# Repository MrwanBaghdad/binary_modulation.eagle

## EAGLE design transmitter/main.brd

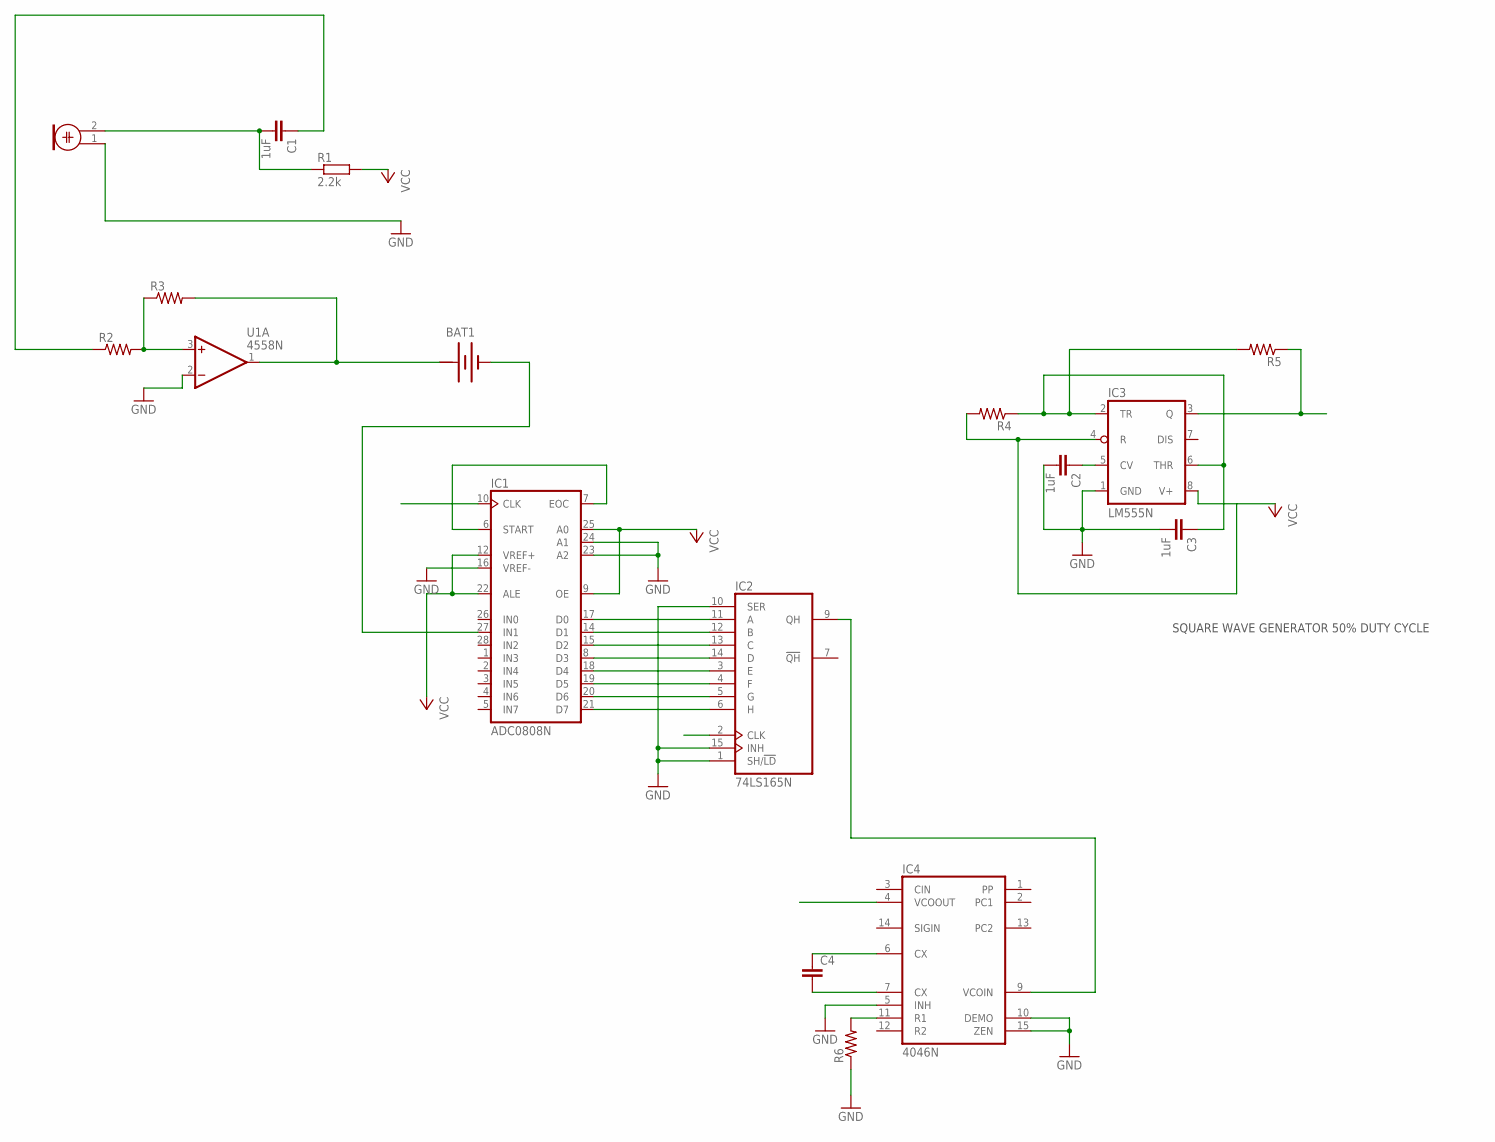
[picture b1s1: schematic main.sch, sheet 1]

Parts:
BAT1: BATTERY
C1, C2, C3: 1uF; C2.5-3
C4: C2.5/2; C2.5-2
IC1: ADC0808N; DIL28-6
IC2: 74LS165N; DIL16
IC3: LM555N; DIL08-ROUND
IC4: 4046N; DIL16
M1: ELECTRET_MICROPHON-F6050AP; F6050AP
R1: 2.2k; 0204/7
R2, R3, R4, R5, R6: R-US_0204/7; 0204/7
U1: 4558N; DIL08

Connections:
+: BAT1.+@1 (+)
CLK: IC1.10 (CLK), IC2.2 (CLK), IC3.3 (Q), R5.1
GND: C2.2, C3.2, IC1.13 (GND), IC1.16 (VREF-), IC1.23 (A2), IC1.24 (A1), IC2.1 (SH/!LD), IC2.8 (GND), IC2.10 (SER), IC2.15 (INH), IC3.1 (GND), IC4.5 (INH), IC4.10 (DEMO), IC4.15 (ZEN), M1.1, R6.1, U1.2 (-IN)
unnamed: C1.2, M1.2, R1.1
unnamed: C1.1, R2.1
unnamed: R2.2, R3.1, U1.3 (+IN)
unnamed: BAT1.+, R3.2, U1.1 (OUT)
unnamed: BAT1.-, IC1.27 (IN1)
unnamed: IC1.6 (START), IC1.7 (EOC)
unnamed: IC1.17 (D0), IC2.11 (A)
unnamed: IC1.14 (D1), IC2.12 (B)
unnamed: IC1.15 (D2), IC2.13 (C)
unnamed: IC1.8 (D3), IC2.14 (D)
unnamed: IC1.18 (D4), IC2.3 (E)
unnamed: IC1.19 (D5), IC2.4 (F)
unnamed: IC1.20 (D6), IC2.5 (G)
unnamed: IC1.21 (D7), IC2.6 (H)
unnamed: IC2.9 (QH), IC4.9 (VCOIN)
unnamed: C2.1, IC3.5 (CV)
unnamed: C4.1, IC4.6 (CX)
unnamed: C3.1, IC3.2 (TR), IC3.6 (THR), R4.1, R5.2
unnamed: C4.2, IC4.7 (CX)
unnamed: IC4.11 (R1), R6.2
VCC: IC1.9 (OE), IC1.11 (VCC), IC1.12 (VREF+), IC1.22 (ALE), IC1.25 (A0), IC2.16 (VCC), IC3.4 (R), IC3.8 (V+), R1.2, R4.2
VCC+: U1.8 (VCC+)
VCC-: U1.4 (VCC-)
VDD: IC4.16 (VDD)
VSS: IC4.8 (VSS)

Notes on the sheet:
SQUARE WAVE GENERATOR 50% DUTY CYCLE

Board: 2 copper layers, 17 parts (0 on the bottom side), 23 nets, no tracks yet.

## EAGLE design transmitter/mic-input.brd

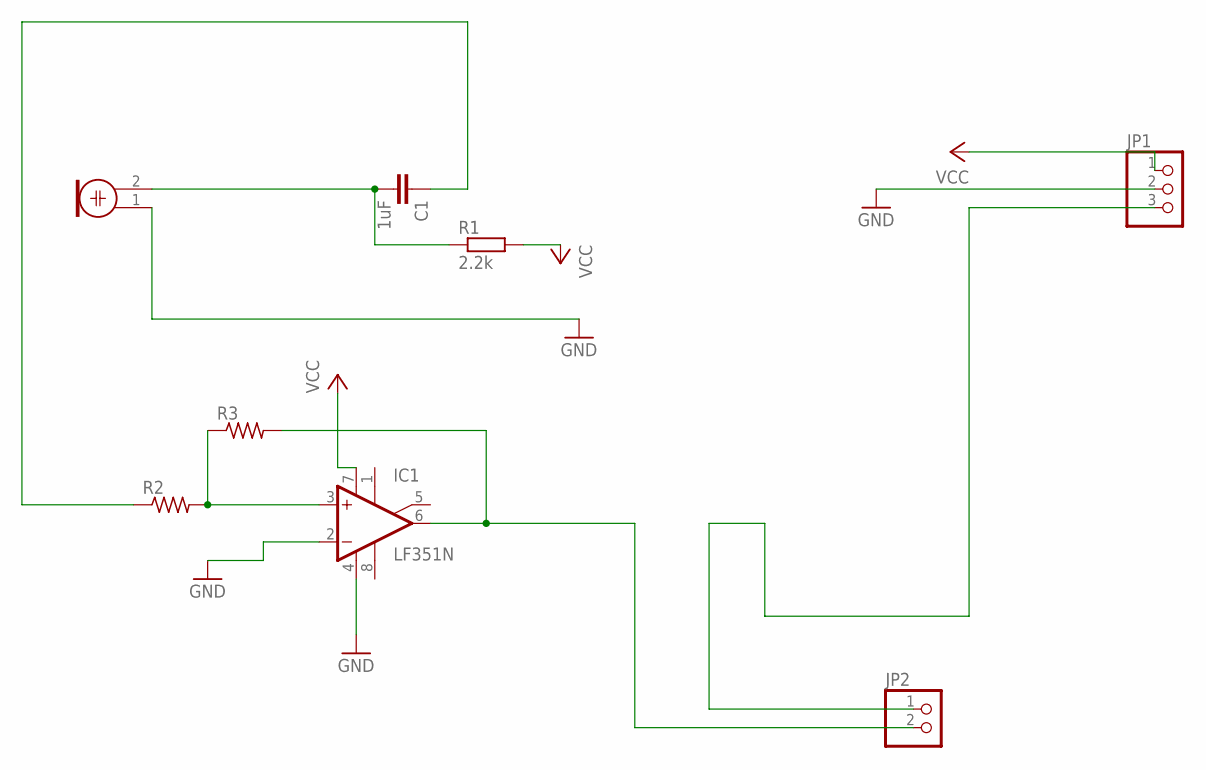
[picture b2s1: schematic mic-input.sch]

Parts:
C1: 1uF; C2.5-3
IC1: LF351N; DIL08
JP1: PINHD-1X3; 1X03
JP2: PINHD-1X2; 1X02
M1: ELECTRET_MICROPHON-F6050AP; F6050AP
R1: 2.2k; 0204/7
R2, R3: R-US_0204/7; 0204/7

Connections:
GND: IC1.2 (-IN), IC1.4 (V-), JP1.2, M1.1
unnamed: C1.2, M1.2, R1.1
unnamed: C1.1, R2.1
unnamed: IC1.3 (+IN), R2.2, R3.1
unnamed: IC1.6 (OUT), JP2.2, R3.2
unnamed: JP1.3, JP2.1
VCC: IC1.7 (V+), JP1.1, R1.2

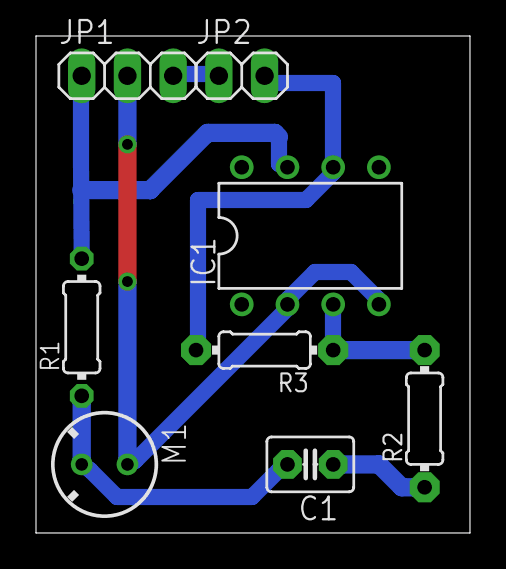
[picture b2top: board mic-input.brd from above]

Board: 2 copper layers, 24.1 x 27.6 mm, 8 parts (0 on the bottom side), 7 nets.

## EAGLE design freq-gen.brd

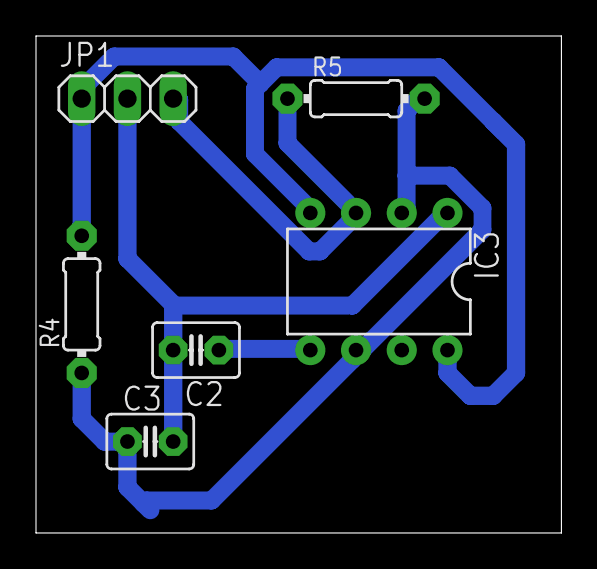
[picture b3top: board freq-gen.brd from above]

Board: 2 copper layers, 29.2 x 27.6 mm, 6 parts (0 on the bottom side), 5 nets.

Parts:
C2, C3: 1uF; C2.5-3
IC3: LM555N; DIL08-ROUND
JP1: 1X03
R4, R5: 0204/7

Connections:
CLK: IC3.3, JP1.3, R5.1
GND: C2.2, C3.2, IC3.1, JP1.2
unnamed: C2.1, IC3.5
unnamed: C3.1, IC3.2, IC3.6, R4.1, R5.2
VCC: IC3.4, IC3.8, JP1.1, R4.2

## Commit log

2017-06-17 init
2017-06-19 moved to tras folder, added pll circuit
2017-06-19 moved file to tran* folder

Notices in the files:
parts and their libraries:
op-amp: Copyright (C) 2015, Bob Starr
